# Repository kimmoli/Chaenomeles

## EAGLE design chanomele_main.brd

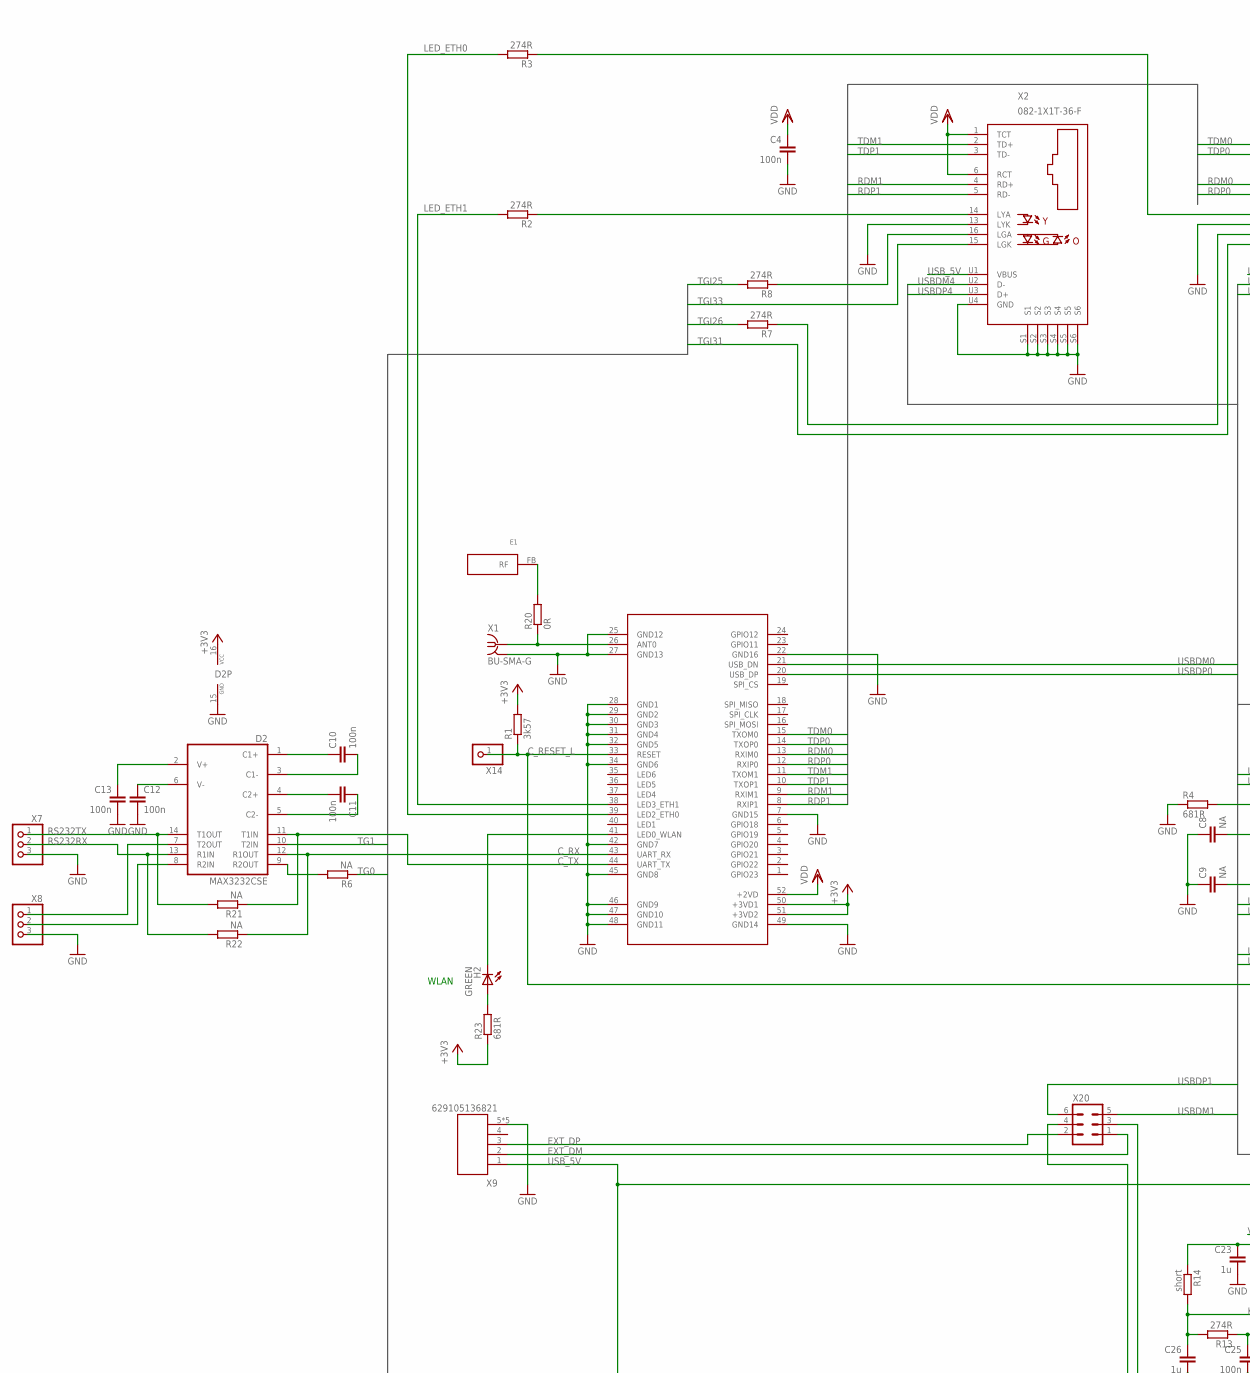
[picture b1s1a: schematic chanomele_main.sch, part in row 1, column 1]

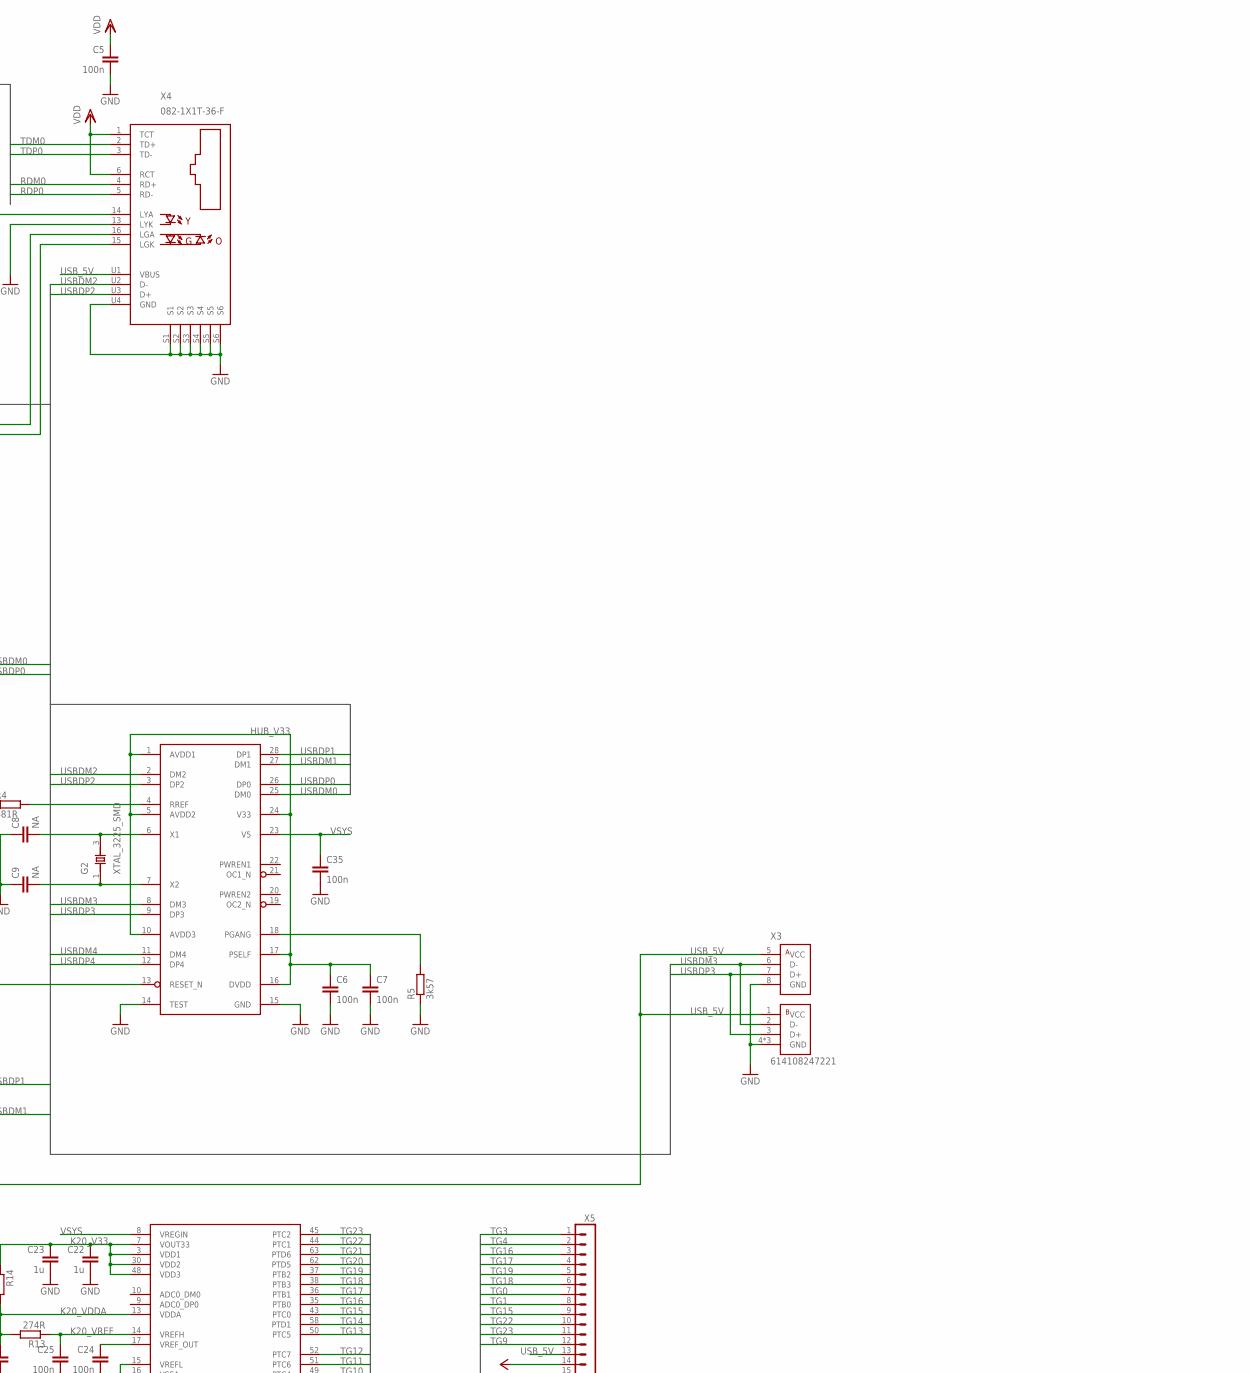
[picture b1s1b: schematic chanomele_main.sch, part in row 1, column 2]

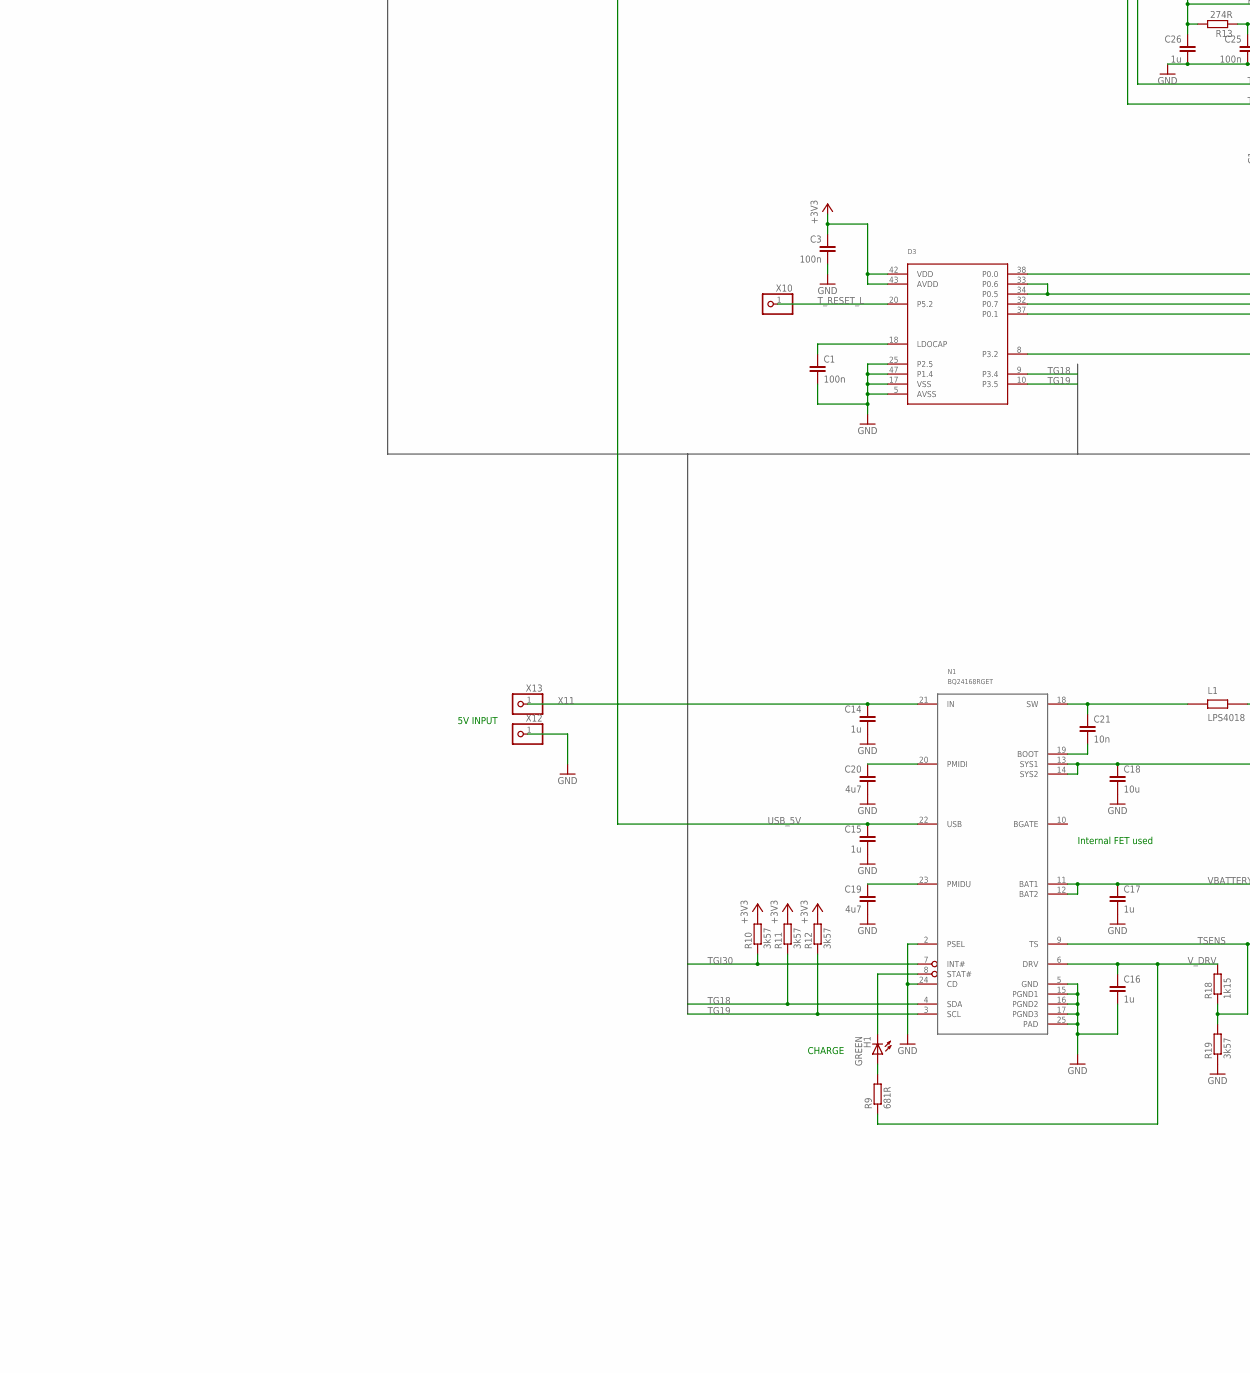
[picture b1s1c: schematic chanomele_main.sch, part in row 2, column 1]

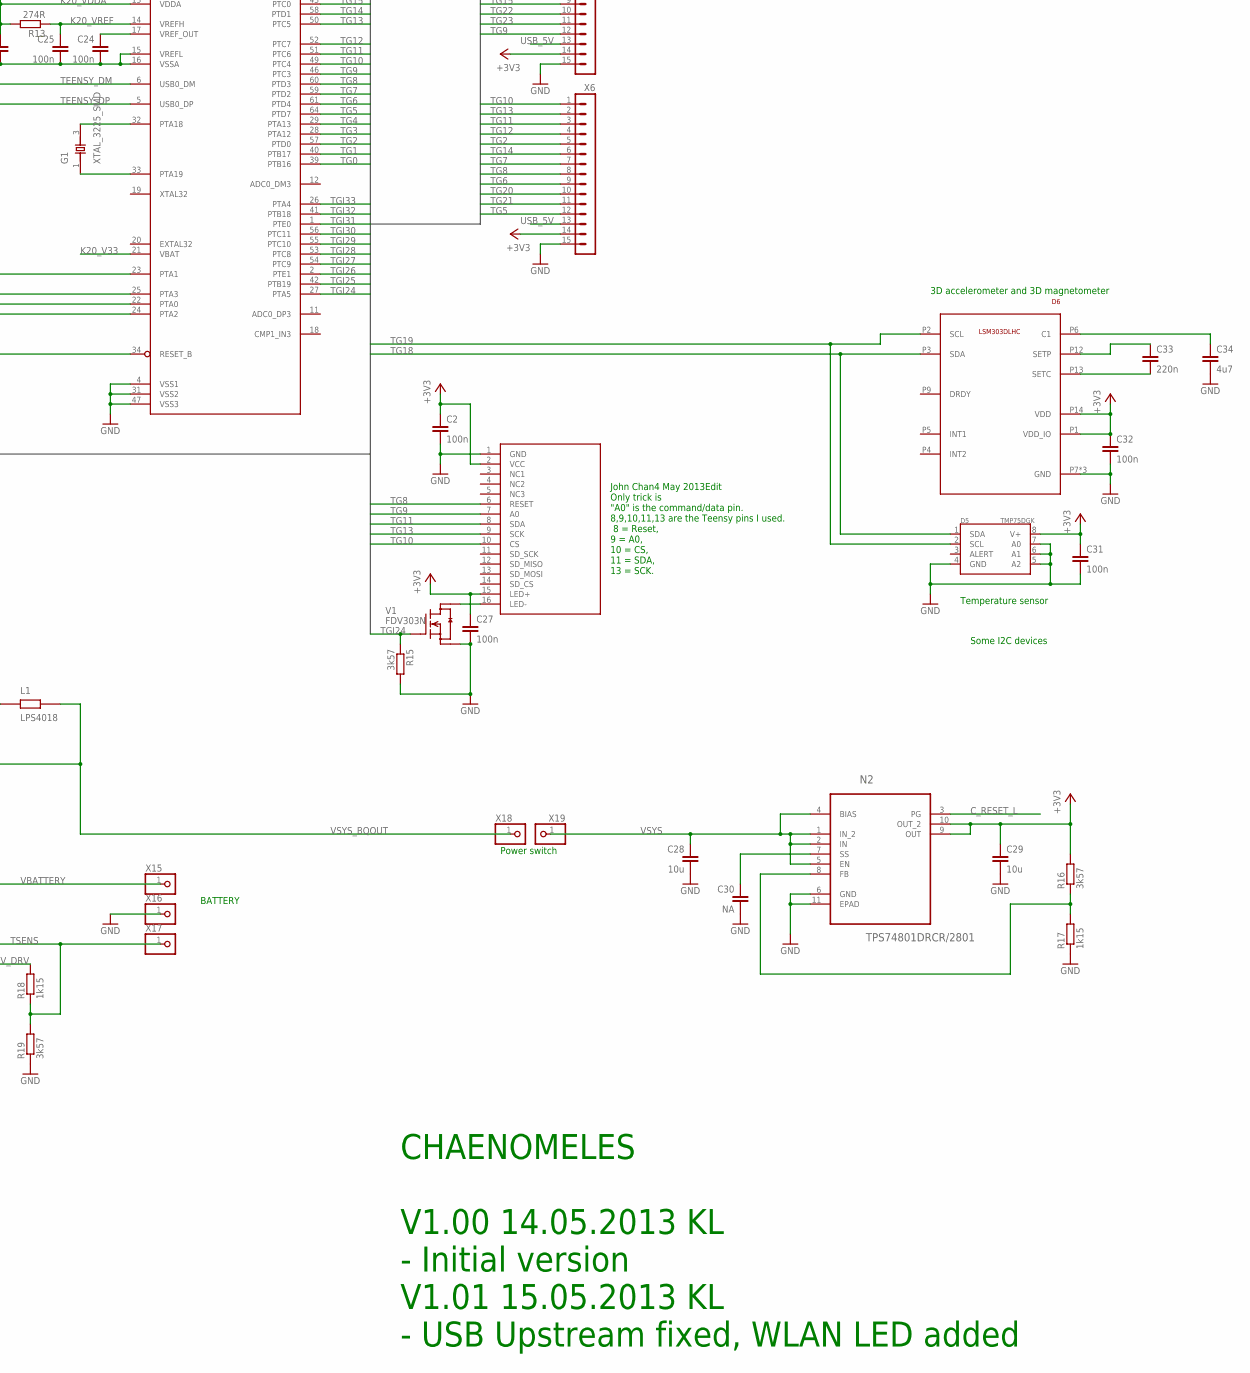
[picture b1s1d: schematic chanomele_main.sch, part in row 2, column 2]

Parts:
A1: CARAMBOLA2; CARAMBOLA1
A2: TFT18
C1, C2, C3, C4, C5, C6, C7, C10, C11, C12, C13, C24, C25, C27, C31, C32, C35: 100n; C0402
C8, C9, C30: NA; C0402
C14, C15, C16, C17, C22, C23, C26: 1u; C0603
C18, C28, C29: 10u; C0805
C19, C20, C34: 4u7; C0805
C21: 10n; C0402
C33: 220n; C0402
D1: MK20DX128VLH5; FREESCALE_64_LQFP
D2: MAX3232CSE; SO16
D3: MINI54LAN; LQFP48-7X7
D4: GL850G; SSOP28DB
D5: TMP75DGK; MSOP8
D6: LSM303DLHC; LGA_3X5X1_14L
E1: SMD_ANT_2.4GHZ; 2.4GHZ_SMD_ANTENNA
G1, G2: XTAL_3225_SMD; X_3225
H1, H2: GREEN; CHIP-LED0603
L1: LPS4018
N1: BQ24168RGET; QFN50P400X400X100-25N
N2: TPS74801DRCR/2801; SON50P300X300X100-11N
R1, R5, R10, R11, R12, R15, R16, R19: 3k57; R0402
R2, R3, R7, R8, R13: 274R; R0402
R4, R9, R23: 681R; R0402
R6, R21, R22: NA; R0402
R14: short; R0402
R17, R18: 1k15; R0402
R20: 0R; R0402
V1: FDV303N; SOT23
X1: BU-SMA-G
X2, X4: 082-1X1T-36-F; 0821-1X1T-36-F
X3: 614108247221
X5, X6: PIIKKIRIMA-15
X7, X8: PINHD-1X3/90; 1X03/90
X9: 629105136821
X10, X12, X13, X14, X15, X16, X17, X18, X19: PINHD-1X1; 1X01
X20: MA03-2

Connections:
+3V3: A1.50 (+3VD1), A1.51 (+3VD2), A2.2 (VCC), A2.15 (LED+), C2.1, C3.1, C27.1, C29.1, C31.1, C32.1, D2.16 (VCC), D3.42 (VDD), D3.43 (AVDD), D5.8 (V+), D6.P1 (VDD_IO), D6.P14 (VDD), N2.9 (OUT), N2.10 (OUT_2), R1.2, R10.2, R11.2, R12.2, R16.2, R23.1, X5.14, X6.14
C_RESET_L: A1.33 (RESET), D4.13 (RESET_N), N2.3 (PG), R1.1, X14.1
C_RX: A1.43 (UART_RX), D2.12 (R1OUT), R22.1
C_TX: A1.44 (UART_TX), D2.11 (T1IN), R21.1
EXTAL: D1.33 (PTA19), G1.1 (X1)
EXT_DM: X9.2, X20.1
EXT_DP: X9.3, X20.2
FEEDBACK: N2.8 (FB), R16.1, R17.2
GND: A1.7 (GND15), A1.22 (GND16), A1.25 (GND12), A1.27 (GND13), A1.28 (GND1), A1.29 (GND2), A1.30 (GND3), A1.31 (GND4), A1.32 (GND5), A1.34 (GND6), A1.42 (GND7), A1.45 (GND8), A1.46 (GND9), A1.47 (GND10), A1.48 (GND11), A1.49 (GND14), A2.1 (GND), C1.2, C2.2, C3.2, C4.2, C5.2, C6.2, C7.2, C8.1, C9.1, C12.2, C13.2, C14.2, C15.2, C16.2, C17.2, C18.2, C19.2, C20.2, C22.2, C23.2, C24.2, C25.2, C26.2, C27.2, C28.2, C29.2, C30.2, C31.2, C32.2, C34.2, C35.2, D1.4 (VSS1), D1.15 (VREFL), D1.16 (VSSA), D1.31 (VSS2), D1.47 (VSS3), D2.15 (GND), D3.5 (AVSS), D3.17 (VSS), D3.25 (P2.5), D3.47 (P1.4), D4.14 (TEST), D4.15 (GND), D5.4 (GND), D5.5 (A2), D5.6 (A1), D5.7 (A0), D6.P7 (GND), D6.P10 (GND), D6.P11 (GND), N1.2 (PSEL), N1.5 (GND), N1.15 (PGND1), N1.16 (PGND2), N1.17 (PGND3), N1.24 (CD), N1.25 (PAD), N2.6 (GND), N2.11 (EPAD), R4.1, R5.1, R15.2, R17.1, R19.1, V1.2 (S), X1.2, X1.3 (2), X1.4 (2), X1.5 (2), X2.13 (LYK), X2.S1, X2.S2, X2.S3, X2.S4, X2.S5, X2.S6, X2.U4 (GND), X3.4 (GND), X3.8 (GND), X3.P$1 (GND), X3.P$2 (GND), X4.13 (LYK), X4.S1, X4.S2, X4.S3, X4.S4, X4.S5, X4.S6, X4.U4 (GND), X5.15, X6.15, X7.3, X8.3, X9.5, X9.Z1 (5), X9.Z2 (5), X9.Z3 (5), X9.Z4 (5), X12.1, X16.1
HUB_V33: C6.1, C7.1, D4.1 (AVDD1), D4.5 (AVDD2), D4.10 (AVDD3), D4.16 (DVDD), D4.17 (PSELF), D4.24 (V33)
K20_V33: C22.1, C23.1, D1.3 (VDD1), D1.7 (VOUT33), D1.21 (VBAT), D1.30 (VDD2), D1.48 (VDD3), R14.1
K20_VDDA: C26.1, D1.13 (VDDA), R13.2, R14.2
K20_VREF: C25.1, D1.14 (VREFH), R13.1
LED_ETH0: A1.39 (LED2_ETH0), R3.2
LED_ETH1: A1.38 (LED3_ETH1), R2.2
LED_WLAN: A1.41 (LED0_WLAN), H2.C
unnamed: D1.23 (PTA1), D3.38 (P0.0)
unnamed: D1.25 (PTA3), D3.33 (P0.6), D3.34 (P0.5)
unnamed: A1.26 (ANT0), R20.1, X1.1
unnamed: C8.2, D4.6 (X1), G2.3 (X2)
unnamed: C9.2, D4.7 (X2), G2.1 (X1)
unnamed: E1.FB, R20.2
unnamed: D1.22 (PTA0), D3.32 (P0.7)
unnamed: D1.24 (PTA2), D3.37 (P0.1)
unnamed: D1.34 (RESET_B), D3.8 (P3.2)
unnamed: C1.1, D3.18 (LDOCAP)
unnamed: R2.1, X2.14 (LYA)
unnamed: R3.1, X4.14 (LYA)
unnamed: H2.A, R23.2
unnamed: D4.18 (PGANG), R5.2
unnamed: C12.1, D2.6 (V-)
unnamed: C13.1, D2.2 (V+)
unnamed: C10.1, D2.1 (C1+)
unnamed: C10.2, D2.3 (C1-)
unnamed: C11.1, D2.5 (C2-)
unnamed: C11.2, D2.4 (C2+)
unnamed: D2.7 (T2OUT), X8.1
unnamed: D2.8 (R2IN), X8.2
unnamed: D2.9 (R2OUT), R6.2
unnamed: R7.1, X4.16 (LGA)
unnamed: R8.1, X2.16 (LGA)
unnamed: C20.1, N1.20 (PMIDI)
unnamed: C19.1, N1.23 (PMIDU)
unnamed: C21.2, N1.19 (BOOT)
unnamed: C24.1, D1.17 (VREF_OUT)
unnamed: C21.1, L1.A, N1.18 (SW)
unnamed: H1.C, N1.8 (STAT#)
unnamed: H1.A, R9.2
unnamed: A2.16 (LED-), V1.3 (D)
unnamed: C34.1, D6.P6 (C1)
unnamed: C33.2, D6.P13 (SETC)
unnamed: C33.1, D6.P12 (SETP)
RDM0: A1.13 (RXIM0), X4.4 (RD+)
RDM1: A1.9 (RXIM1), X2.4 (RD+)
RDP0: A1.12 (RXIP0), X4.5 (RD-)
RDP1: A1.8 (RXIP1), X2.5 (RD-)
RS232RX: D2.13 (R1IN), R22.2, X7.2
RS232TX: D2.14 (T1OUT), R21.2, X7.1
SS: C30.1, N2.7 (SS)
TDM0: A1.15 (TXOM0), X4.2 (TD+)
TDM1: A1.11 (TXOM1), X2.2 (TD+)
TDP0: A1.14 (TXOP0), X4.3 (TD-)
TDP1: A1.10 (TXOP1), X2.3 (TD-)
TEENSY_DM: D1.6 (USB0_DM), X20.3
TEENSY_DP: D1.5 (USB0_DP), X20.4
TG0: D1.39 (PTB16), R6.1, X5.7
TG1: D1.40 (PTB17), D2.10 (T2IN), X5.8
TG2: D1.57 (PTD0), X6.5
TG3: D1.28 (PTA12), X5.1
TG4: D1.29 (PTA13), X5.2
TG5: D1.64 (PTD7), X6.12
TG6: D1.61 (PTD4), X6.9
TG7: D1.59 (PTD2), X6.7
TG8: A2.6 (RESET), D1.60 (PTD3), X6.8
TG9: A2.7 (A0), D1.46 (PTC3), X5.12
TG10: A2.10 (CS), D1.49 (PTC4), X6.1
TG11: A2.8 (SDA), D1.51 (PTC6), X6.3
TG12: D1.52 (PTC7), X6.4
TG13: A2.9 (SCK), D1.50 (PTC5), X6.2
TG14: D1.58 (PTD1), X6.6
TG15: D1.43 (PTC0), X5.9
TG16: D1.35 (PTB0), X5.3
TG17: D1.36 (PTB1), X5.4
TG18: D1.38 (PTB3), D3.9 (P3.4), D5.1 (SDA), D6.P3 (SDA), N1.4 (SDA), R11.1, X5.6
TG19: D1.37 (PTB2), D3.10 (P3.5), D5.2 (SCL), D6.P2 (SCL), N1.3 (SCL), R12.1, X5.5
TG20: D1.62 (PTD5), X6.10
TG21: D1.63 (PTD6), X6.11
TG22: D1.44 (PTC1), X5.10
TG23: D1.45 (PTC2), X5.11
TGI24: D1.27 (PTA5), R15.1, V1.1 (G)
TGI25: D1.42 (PTB19), R8.2
TGI26: D1.2 (PTE1), R7.2
TGI27: D1.54 (PTC9)
TGI28: D1.53 (PTC8)
TGI29: D1.55 (PTC10)
TGI30: D1.56 (PTC11), N1.7 (INT#), R10.1
TGI31: D1.1 (PTE0), X4.15 (LGK)
TGI32: D1.41 (PTB18)
TGI33: D1.26 (PTA4), X2.15 (LGK)
TSENS: N1.9 (TS), R18.1, R19.2, X17.1
T_RESET_L: D3.20 (P5.2), X10.1
USBDM0: A1.21 (USB_DN), D4.25 (DM0)
USBDM1: D4.27 (DM1), X20.5
USBDM2: D4.2 (DM2), X4.U2 (D-)
USBDM3: D4.8 (DM3), X3.2 (D-), X3.6 (D-)
USBDM4: D4.11 (DM4), X2.U2 (D-)
USBDP0: A1.20 (USB_DP), D4.26 (DP0)
USBDP1: D4.28 (DP1), X20.6
USBDP2: D4.3 (DP2), X4.U3 (D+)
USBDP3: D4.9 (DP3), X3.3 (D+), X3.7 (D+)
USBDP4: D4.12 (DP4), X2.U3 (D+)
USBREF: D4.4 (RREF), R4.2
USB_5V: C15.1, N1.22 (USB), X2.U1 (VBUS), X3.1 (VCC), X3.5 (VCC), X4.U1 (VBUS), X5.13, X6.13, X9.1
VBATTERY: C17.1, N1.11 (BAT1), N1.12 (BAT2), X15.1
VDD: A1.52 (+2VD), C4.1, C5.1, X2.1 (TCT), X2.6 (RCT), X4.1 (TCT), X4.6 (RCT)
VSYS: C28.1, C35.1, D1.8 (VREGIN), D4.23 (V5), N2.1 (IN_2), N2.2 (IN), N2.4 (BIAS), N2.5 (EN), X19.1
VSYS_BQOUT: C18.1, L1.B, N1.13 (SYS1), N1.14 (SYS2), X18.1
V_DRV: C16.1, N1.6 (DRV), R9.1, R18.2
X11: C14.1, N1.21 (IN), X13.1
XTAL: D1.32 (PTA18), G1.3 (X2)

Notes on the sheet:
John Chan4 May 2013Edit Only trick is "A0" is the command/data pin. 8,9,10,11,13 are the Teensy pins I used. 8 = Reset, 9 = A0, 10 = CS, 11 = SDA, 13 = SCK.
BATTERY
5V INPUT
CHARGE
Internal FET used
Power switch
Some I2C devices
Temperature sensor
3D accelerometer and 3D magnetometer
CHAENOMELES V1.00 14.05.2013 KL - Initial version V1.01 15.05.2013 KL - USB Upstream fixed, WLAN LED added
WLAN

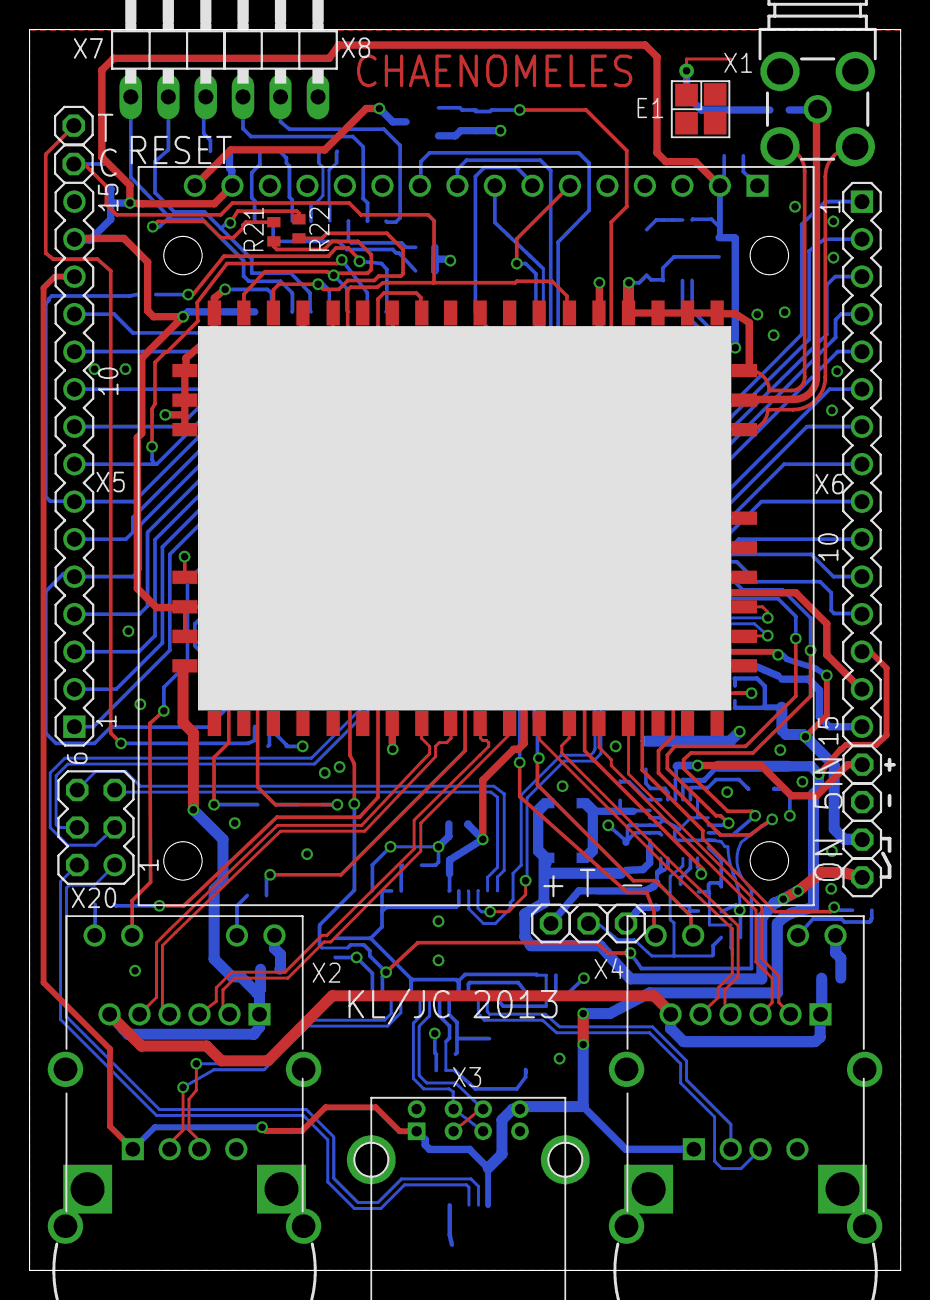
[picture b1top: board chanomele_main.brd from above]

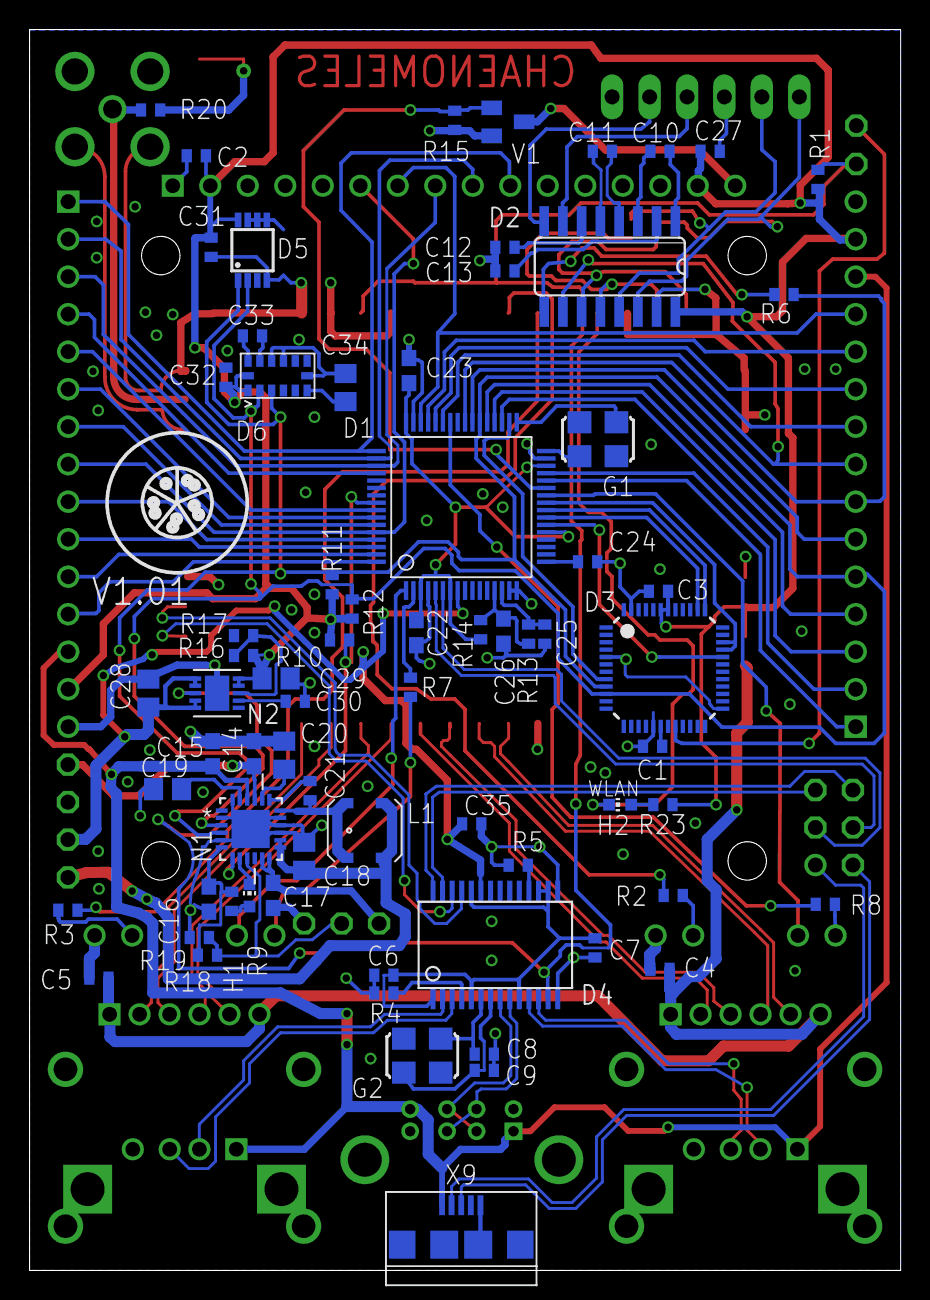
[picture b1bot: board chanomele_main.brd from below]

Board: 2 copper layers, 59.0 x 84.0 mm, 94 parts (71 on the bottom side), 116 nets.

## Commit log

2013-06-14 V1.01
